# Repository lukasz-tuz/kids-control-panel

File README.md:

# kids-control-panel

This project is a spaceship-like control panel toy for kids (of all ages) allowing to:

* display characters from the alphanumeric keypad on the 7-segment display
* turn on LEDs in the 8x8 matrix when keys are pressed on the 4x4 keypad
* display some patterns using the 4-color LED bar
* use four tactile buttons to switch modes of operation for joystick and encoder:
  * control the LED bar
  * control the RGB LED's color
  * control LEDs on the 8x8 matrix
  
Repository contains FreeCAD designs for the casing (inteded for wood laser cutters), KiCAD schematics for the electronics part, and code for Arduino Uno R3 board.

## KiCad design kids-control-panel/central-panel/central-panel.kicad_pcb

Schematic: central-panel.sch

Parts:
C1, C2: 100pF; C_0603_1608Metric; LCSC C1635
C3: 100uF; C_1206_3216Metric; LCSC C15008
C4: 10nF; C_0603_1608Metric; LCSC C57112
D1, D2, D3: LED; LED_0603_1608Metric; LCSC C72038
D4, D5, D6: LED; LED_0603_1608Metric; LCSC C72043
D7, D8, D9: LED; LED_0603_1608Metric; LCSC C2286
D10, D11, D12: LED; LED_0603_1608Metric; LCSC C72041
D13: LED_EN_A; LED_Inolux_IN-PI554FCH_PLCC4_5.0x5.0mm_P3.2mm; LCSC C139127
D14: LED_EN_B; LED_Inolux_IN-PI554FCH_PLCC4_5.0x5.0mm_P3.2mm; LCSC C139127
H1, H2, H3, H4: MountingHole; MountingHole_2.2mm_M2
J1: Conn_01x06; PinHeader_1x06_P2.54mm_Horizontal
J4: Arduino_Conn; PinHeader_1x06_P2.54mm_Horizontal
R1, R2, R3, R4: 220; R_0603_1608Metric; LCSC C22962
R5, R6: 10k; R_0603_1608Metric; LCSC C25804
SW1, SW2: SW_SPST_LED; PinSocket_1x03_P2.54mm_Vertical
TP1, TP2, TP3, TP4, TP5, TP6: TestPoint; TestPoint_Plated_Hole_D2.0mm
U1: CA56-12EWA
U2: TM1637; SOP-20_7.5x12.8mm_P1.27mm; LCSC C20001

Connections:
/CA1: U1.12, U2.15
/CA2: U1.9, U2.14
/CA3: U1.8, U2.13
/CA4: U1.6, U2.12
/CLK: C1.1, J4.3, R5.2, U2.18
/DIO: C2.1, J4.2, R6.2, U2.17
/DPX: U1.3, U2.9
/ENABLE_A: J4.4, SW1.3
/ENABLE_B: J4.5, SW2.3
/LED_A: J1.3, R4.2
/LED_B: J1.4, R1.2
/LED_C: J1.5, R2.2
/LED_D: J1.6, R3.2
/LED_EN_A: D13.2, J1.1
/LED_EN_B: D14.2, J1.2
/SEG_A: U1.11, U2.2
/SEG_B: U1.7, U2.3
/SEG_C: U1.4, U2.4
/SEG_D: U1.2, U2.5
/SEG_E: U1.1, U2.6
/SEG_F: U1.10, U2.7
/SEG_G: U1.5, U2.8
GND: C1.2, C2.2, C3.2, C4.2, D1.1 (K), D2.1 (K), D3.1 (K), D4.1 (K), D5.1 (K), D6.1 (K), D7.1 (K), D8.1 (K), D9.1 (K), D10.1 (K), D11.1 (K), D12.1 (K), D13.1, D14.1, J4.1, SW1.2, SW2.2, TP5.1, U2.1
unnamed: D1.2 (A), D2.2 (A), D3.2 (A), R4.1, TP1.1
unnamed: D4.2 (A), D5.2 (A), D6.2 (A), R1.1, TP2.1
unnamed: D7.2 (A), D8.2 (A), D9.2 (A), R2.1, TP3.1
unnamed: D10.2 (A), D11.2 (A), D12.2 (A), R3.1, TP4.1
VCC: C3.1, C4.1, D13.3, D14.3, J4.6, R5.1, R6.1, SW1.1, SW2.1, TP6.1, U2.16

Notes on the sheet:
Mounting holes

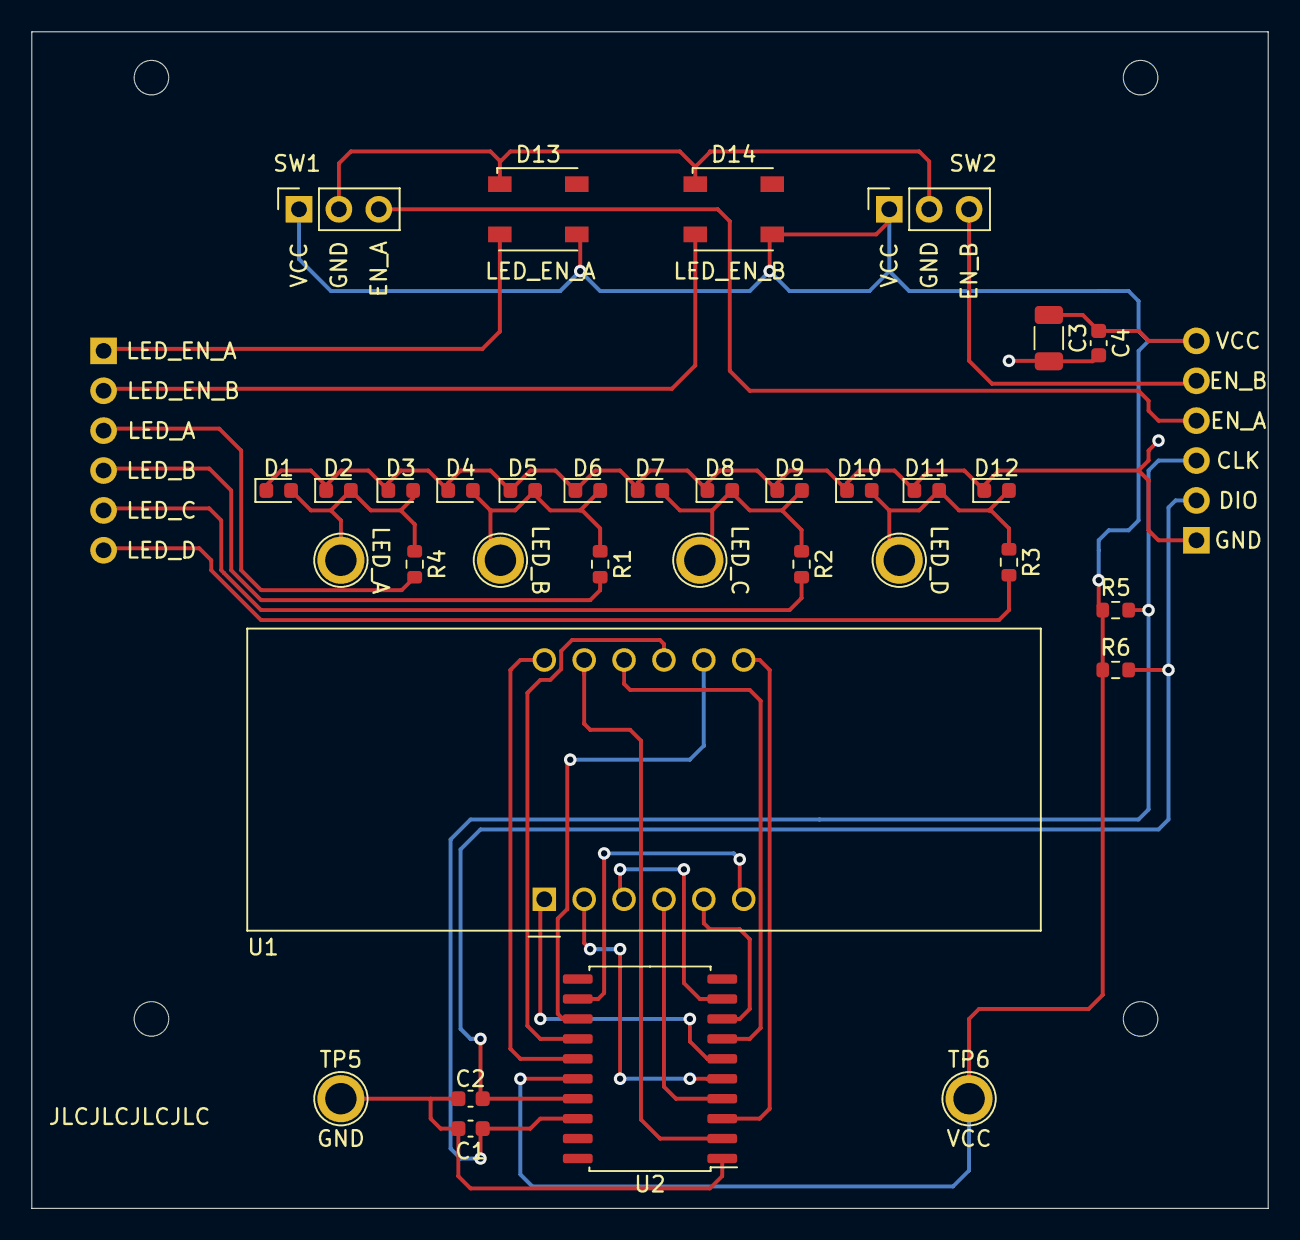
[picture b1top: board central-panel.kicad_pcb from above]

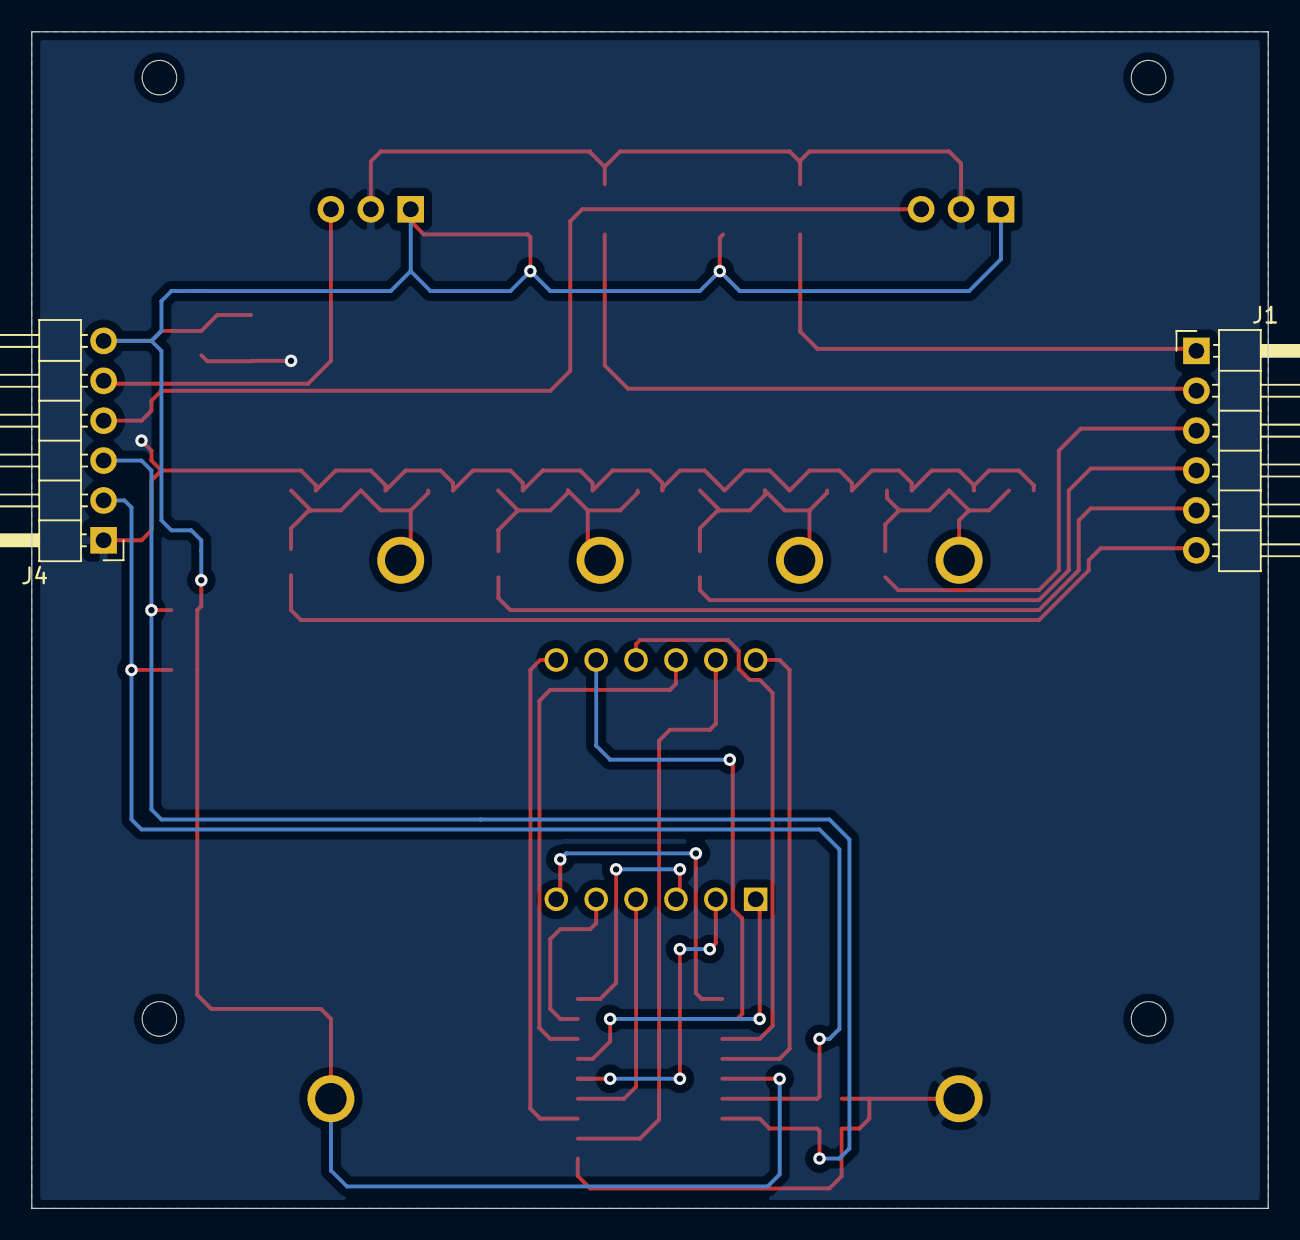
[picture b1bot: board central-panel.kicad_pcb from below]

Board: 2 copper layers, 78.7 x 74.9 mm, 40 parts (2 on the bottom side), 28 nets.

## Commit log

2021-04-04 fixing pin assignment for keypad
2021-04-11 updating preferences for cpp
2021-04-11 cad file changes
2021-04-11 Custome central panel PCB
2021-04-11 Ino sketch, working buttons and switches
2021-04-18 Adding modes, color selection, led bar support
2021-04-19 Assignment of pins to led bar breaks stuff
2021-04-21 Directory structure cleanup
2021-04-21 vscode workspace initialization
2021-04-21 Adding comments
2021-04-21 Initial commit of TFT paint sketch
2021-04-23 Adding wrapper class for joystick
2021-04-29 HW components enabling done (without LCD). Added drawings and photos to export directory
2021-05-01 Enabling of 1st version of HW
2021-05-01 Fixing defines with parenthesis
2021-05-02 Cleanup and resize of images and export collaterals
2021-05-03 Removing lingering comment in a header file. Downscaling images.
2021-05-03 Adding a demo video
2021-05-03 Create LICENSE
2021-11-26 adding .vscode to gitignore
2021-11-26 removing additional .vscode directories
2021-11-26 Adding separate license to CAD files (CC BY 4.0)
2021-11-26 Adding separate LICENSE file to directories with code
